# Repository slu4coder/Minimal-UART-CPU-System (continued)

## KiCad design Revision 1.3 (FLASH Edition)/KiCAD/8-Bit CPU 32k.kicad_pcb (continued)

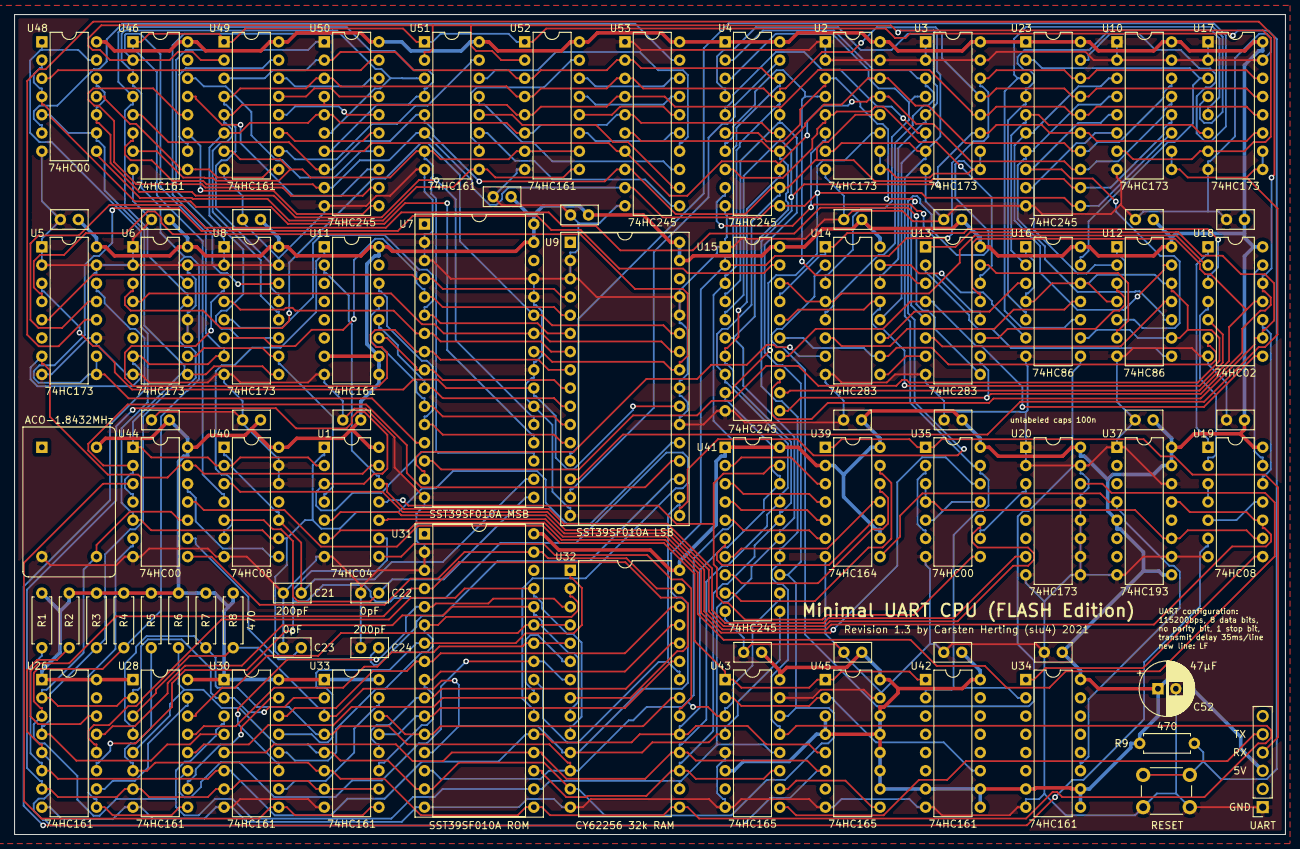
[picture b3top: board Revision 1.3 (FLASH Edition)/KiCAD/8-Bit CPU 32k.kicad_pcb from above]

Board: 2 copper layers, 177.2 x 114.3 mm, 81 parts (0 on the bottom side), 157 nets.

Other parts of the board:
U2, U3: 74HC173; DIP-16_W7.62mm
U4, U15: 74HC245; DIP-20_W7.62mm
U12, U16: 74HC86; DIP-14_W7.62mm
U13, U14: 74HC283; DIP-16_W7.62mm
U18: 74HC02; DIP-14_W7.62mm
U42: 74HC161; DIP-16_W7.62mm
U43, U45: 74HC165; DIP-16_W7.62mm

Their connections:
1.8432MHz: U2.7, U3.7, U42.2; also elsewhere on the board
+5V: U2.16, U3.16, U4.1, U4.20, U12.14, U13.16, U14.16, U15.20, U16.14, U18.14, U42.7, U42.9, U42.10, U42.16, U43.6, U43.16, U45.3, U45.4, U45.10, U45.11, U45.12, U45.13, U45.14, U45.16; also elsewhere on the board
/ALU/A0: U3.3, U4.2, U14.5
/ALU/A1: U3.4, U4.3, U14.3
/ALU/A2: U3.5, U4.4, U14.14
/ALU/A3: U3.6, U4.5, U14.12
/ALU/A4: U2.3, U4.6, U13.5
/ALU/A5: U2.4, U4.7, U13.3
/ALU/A6: U2.5, U4.8, U13.14
/ALU/A7: U2.6, U4.9, U13.12
/ALU/B0: U16.13; also elsewhere on the board
/ALU/B1: U16.10; also elsewhere on the board
/ALU/B2: U16.5; also elsewhere on the board
/ALU/B3: U16.2; also elsewhere on the board
/ALU/B4: U12.13; also elsewhere on the board
/ALU/B5: U12.10; also elsewhere on the board
/ALU/B6: U12.5; also elsewhere on the board
/ALU/B7: U12.2; also elsewhere on the board
/ALU/BUS0: U3.14, U4.18, U15.2, U43.4; also elsewhere on the board
/ALU/BUS1: U3.13, U4.17, U15.3, U43.3; also elsewhere on the board
/ALU/BUS2: U3.12, U4.16, U15.4, U43.14; also elsewhere on the board
/ALU/BUS3: U3.11, U4.15, U15.5, U43.13; also elsewhere on the board
/ALU/BUS4: U2.14, U4.14, U15.6, U43.12; also elsewhere on the board
/ALU/BUS5: U2.13, U4.13, U15.7, U43.11; also elsewhere on the board
/ALU/BUS6: U2.12, U4.12, U15.8, U45.6; also elsewhere on the board
/ALU/BUS7: U2.11, U4.11, U15.9, U45.5; also elsewhere on the board
/ALU/EC: U14.7; also elsewhere on the board
/ALU/ES: U12.1, U12.4, U12.9, U12.12, U16.1, U16.4, U16.9, U16.12; also elsewhere on the board
/ALU/FLAG_C: U13.9; also elsewhere on the board
/ALU/FLAG_N: U13.10, U15.11, U18.12; also elsewhere on the board
/ALU/~EO: U15.19; also elsewhere on the board
/Control Logic/~AI: U2.9, U2.10, U3.9, U3.10; also elsewhere on the board
/Control Logic/~AO: U4.19; also elsewhere on the board
/UART Transmitter/TX: U43.9; also elsewhere on the board
GND: U2.1, U2.2, U2.8, U2.15, U3.1, U3.2, U3.8, U3.15, U4.10, U12.7, U13.8, U14.8, U15.1, U15.10, U16.7, U18.7, U42.8, U43.5, U43.8, U43.15, U45.8, U45.15; also elsewhere on the board
unnamed: U12.3, U13.11
unnamed: U12.6, U13.15
unnamed: U12.8, U13.2
unnamed: U12.11, U13.6
unnamed: U13.1, U15.13, U18.9
unnamed: U13.4, U15.14, U18.8
unnamed: U13.7, U14.9
unnamed: U13.13, U15.12, U18.11
unnamed: U14.1, U15.17, U18.3
unnamed: U14.2, U16.8
unnamed: U14.4, U15.18, U18.2
unnamed: U14.6, U16.11
unnamed: U14.10, U15.15, U18.6
unnamed: U14.11, U16.3
unnamed: U14.13, U15.16, U18.5
unnamed: U14.15, U16.6
unnamed 103: U18.1; also elsewhere on the board
unnamed 104: U18.4; also elsewhere on the board
unnamed 105: U18.10; also elsewhere on the board
unnamed 106: U18.13; also elsewhere on the board
unnamed 129: U42.1, U43.1, U45.1; also elsewhere on the board
unnamed: U42.11, U43.2, U45.2
unnamed: U43.10, U45.9

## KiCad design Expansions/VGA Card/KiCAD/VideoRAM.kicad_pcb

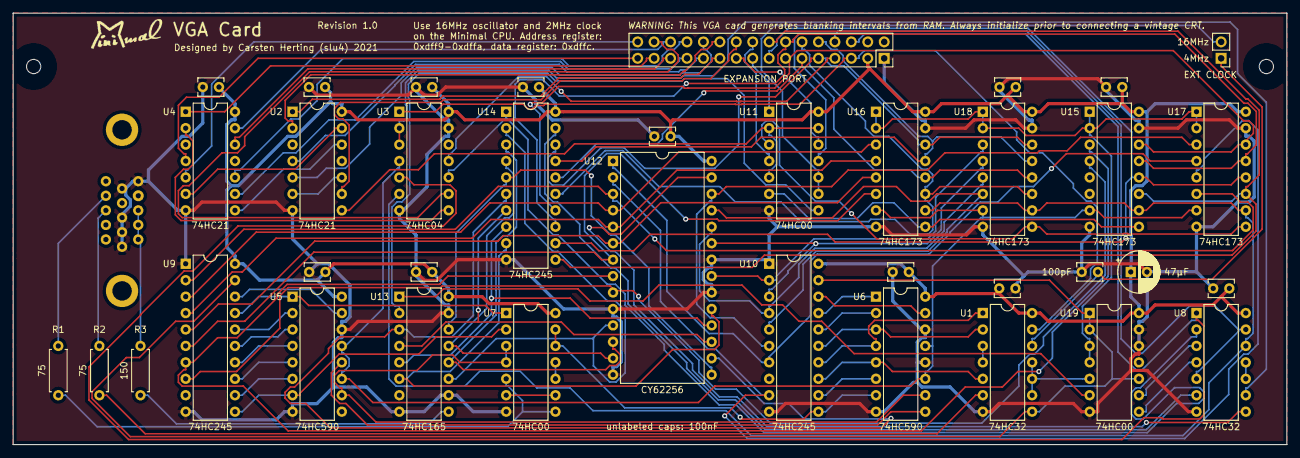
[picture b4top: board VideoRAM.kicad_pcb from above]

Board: 2 copper layers, 196.8 x 66.7 mm, 41 parts (0 on the bottom side), 102 nets.

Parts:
C1: 47µF; CP_Radial_D6.3mm_P2.50mm
C2, C3, C4, C5, C6, C7, C8, C9, C10, C12, C13, C14: 100nF; C_Disc_D3.8mm_W2.6mm_P2.50mm
C11: 100pF; C_Disc_D3.8mm_W2.6mm_P2.50mm
J1: EXPANSION PORT; PinSocket_2x16_P2.54mm_Vertical
J2: VGA connector; VGA DSUB15HD_female
J3: EXT CLOCK; PinHeader_1x02_P2.54mm_Vertical
R1, R2: 75; R_Axial_DIN0207_L6.3mm_D2.5mm_P7.62mm_Horizontal
R3: 150; R_Axial_DIN0207_L6.3mm_D2.5mm_P7.62mm_Horizontal
REF1, REF2: MountingHole_2.2mm_M2
U1, U8: 74HC32; DIP-14_W7.62mm
U2, U4: 74HC21; DIP-14_W7.62mm
U3: 74HC04; DIP-14_W7.62mm
U5, U6: 74HC590; DIP-16_W7.62mm
U7, U11, U19: 74HC00; DIP-14_W7.62mm
U9, U10, U14: 74HC245; DIP-20_W7.62mm
U12: CY62256; DIP-28_W15.24mm
U13: 74HC165; DIP-16_W7.62mm
U15, U16, U17, U18: 74HC173; DIP-16_W7.62mm

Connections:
2MHz: U3.4, U5.11, U5.13, U6.11, U6.13, U15.7, U16.7, U17.7, U18.7
4MHz: C11.1, J3.1, U1.12
16MHz: J3.2, U11.9, U11.10
+5V: C1.1, C2.1, C3.1, C4.1, C5.1, C6.1, C7.1, C8.1, C9.1, C10.1, C12.1, C13.1, C14.1, J1.3, U1.14, U2.14, U3.14, U4.14, U5.16, U6.16, U7.14, U8.14, U9.20, U10.20, U11.14, U12.28, U13.16, U14.20, U15.16, U16.16, U17.16, U18.16, U19.14
/Bus0: J1.9, U14.18, U16.14, U18.14
/Bus1: J1.10, U14.17, U16.13, U18.13
/Bus2: J1.11, U14.16, U16.12, U18.12
/Bus3: J1.12, U14.15, U16.11, U18.11
/Bus4: J1.13, U14.14, U15.14, U17.14
/Bus5: J1.14, U14.13, U15.13, U17.13
/Bus6: J1.15, U14.12, U15.12, U17.12
/Bus7: J1.16, U14.11, U15.11, U17.11
/CLOCK: J1.5, U1.13, U3.1
/H1: U6.15, U10.18
/H2: U6.1, U10.17
/H4: U6.2, U10.16
/H8: U1.2, U6.3, U10.15
/H16: U1.1, U6.4, U10.14
/H32: U1.5, U6.5, U10.13
/M0: J1.17, U11.1
/M1: J1.18, U11.4
/M2: J1.19, U11.12
/M3: J1.20, U2.9
/M4: J1.21, U2.1
/M5: J1.22, U2.2
/M6: J1.23, U2.4
/M7: J1.24, U2.5
/M8: J1.25, U4.9
/M9: J1.26, U4.10
/M10: J1.27, U4.12
/M11: J1.28, U4.13
/M12: J1.29, U4.1
/M13: J1.30, U3.9
/M14: J1.31, U4.4
/M15: J1.32, U4.5
/RI: J1.6, U3.5, U8.1
/RO: U3.10, U8.2, U14.1
/V1: U6.7, U7.12, U7.13, U10.11
/V2: U5.15, U9.18
/V4: U5.1, U7.1, U9.17
/V8: U5.2, U9.16
/V16: U5.3, U9.15
/V32: U5.4, U9.14
/V64: U5.5, U9.13
/V128: U5.6, U9.12
/V256: U5.7, U7.2, U9.11
/VGA_RANGE: U2.8, U11.2, U11.5, U11.13
/~INH: J1.8, U8.5, U8.13, U11.11
/~RI: U3.6, U8.12, U15.10, U16.10, U17.10, U18.10
/~RO: J1.7, U3.11
GND: C1.2, C2.2, C3.2, C4.2, C5.2, C6.2, C7.2, C8.2, C9.2, C10.2, C11.2, C12.2, C13.2, C14.2, J1.1, J2.5, J2.6, J2.7, J2.8, J2.10, U1.7, U2.7, U3.7, U3.13, U4.7, U5.8, U5.14, U6.8, U6.12, U6.14, U7.7, U8.7, U9.1, U9.10, U10.1, U10.10, U11.7, U12.10, U12.14, U12.20, U12.22, U13.8, U13.10, U13.15, U14.10, U15.8, U15.15, U16.8, U16.15, U17.8, U17.15, U18.8, U18.15, U19.7, U19.12, U19.13
unnamed: J2.1, J2.2, J2.3, R3.1
unnamed: J2.13, R2.1
unnamed: J2.14, R1.1
unnamed: R1.2, U7.5, U7.8
unnamed: R2.2, U1.6
unnamed: R3.2, U13.9
unnamed: U1.3, U1.4
unnamed: U1.9, U1.10, U1.11, U19.5
unnamed: U2.6, U2.10
unnamed: U2.12, U4.8
unnamed: U2.13, U4.6
unnamed: U3.8, U4.2
unnamed: U5.10, U6.10, U7.3, U7.4
unnamed: U5.12, U6.9
unnamed: U7.6, U7.9
unnamed: U7.10, U7.11
unnamed: U8.10, U8.11
unnamed: U10.2, U12.21, U18.3
unnamed: U10.3, U12.23, U18.4
unnamed: U10.4, U12.24, U18.5
unnamed: U10.5, U12.25, U18.6
unnamed: U10.6, U12.26, U17.3
unnamed: U10.7, U12.1, U17.4
unnamed: U10.9, U12.2, U17.5
unnamed: U6.6, U10.12
unnamed: U11.3, U17.9, U18.9
unnamed: U11.6, U15.9, U16.9
unnamed: U9.2, U12.3, U17.6
unnamed: U9.3, U12.4, U16.3
unnamed: U9.4, U12.5, U16.4
unnamed: U9.5, U12.6, U16.5
unnamed: U9.6, U12.7, U16.6
unnamed: U9.7, U12.8, U15.3
unnamed: U9.8, U12.9, U15.4
unnamed: U12.11, U13.11, U14.2
unnamed: U12.12, U13.12, U14.3
unnamed: U12.13, U13.13, U14.4
unnamed: U12.15, U13.14, U14.5
unnamed: U12.16, U13.3, U14.6
unnamed: U12.17, U13.4, U14.7
unnamed: U12.18, U13.5, U14.8
unnamed: U12.19, U13.6, U14.9
unnamed: U8.8, U12.27
unnamed: U13.1, U19.6
unnamed: U8.6, U14.19
unnamed: U8.4, U19.8
unnamed: U8.3, U19.9
PIXEL: U11.8, U13.2
T_VRAM: U1.8, U9.19, U10.19, U19.1, U19.2, U19.10
~2MHz: U3.2, U3.3, U8.9
~T_VRAM: U15.1, U15.2, U16.1, U16.2, U17.1, U17.2, U18.1, U18.2, U19.3, U19.4

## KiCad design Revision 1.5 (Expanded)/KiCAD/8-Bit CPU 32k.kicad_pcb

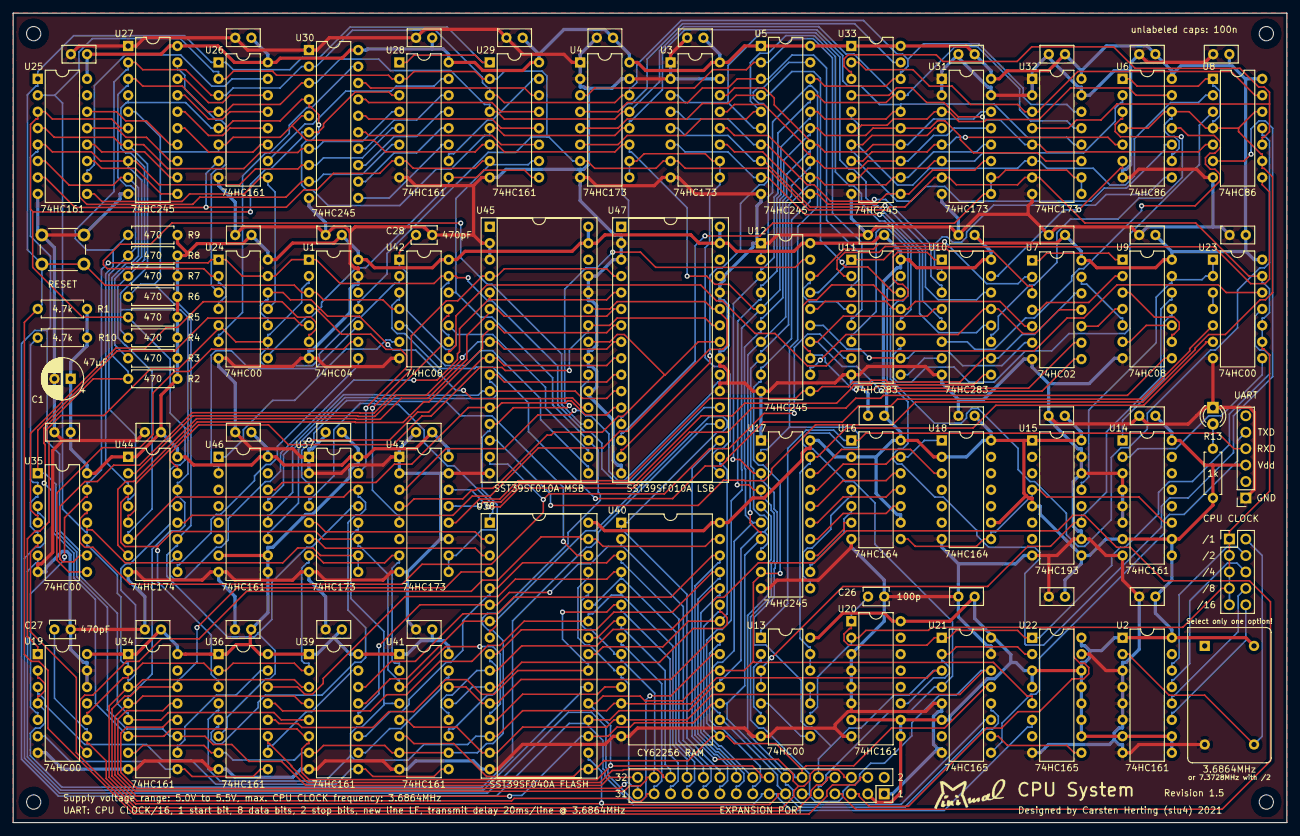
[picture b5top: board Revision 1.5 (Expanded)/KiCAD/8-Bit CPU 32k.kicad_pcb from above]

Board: 2 copper layers, 196.8 x 125.1 mm, 105 parts (0 on the bottom side), 174 nets.

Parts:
C1: 47µF; CP_Radial_D6.3mm_P2.50mm
C2, C3, C4, C5, C6, C7, C8, C9, C10, C11, C12, C13, C14, C15, C16, C17, C18, C19, C20, C21, C22, C23, C24, C25, C29, C30, C31, C32, C33, C34, C35, C36, C37: 100nF; C_Disc_D5.0mm_W2.5mm_P2.50mm
C26: 100p; C_Disc_D3.8mm_W2.6mm_P2.50mm
C27, C28: 470pF; C_Disc_D3.8mm_W2.6mm_P2.50mm
D3: 5V; LED_D3.0mm
H1, H2, H3, H4: M2; MountingHole_2.2mm_M2
J1: UART; PinSocket_1x06_P2.54mm_Vertical
J2: CPU CLOCK; PinHeader_2x05_P2.54mm_Vertical
J3: EXPANSION PORT; PinSocket_2x16_P2.54mm_Vertical
R1, R10: 4.7k; R_Axial_DIN0207_L6.3mm_D2.5mm_P7.62mm_Horizontal
R2, R3, R4, R5, R6, R7, R8, R9: 470; R_Axial_DIN0207_L6.3mm_D2.5mm_P7.62mm_Horizontal
R13: 1k; R_Axial_DIN0207_L6.3mm_D2.5mm_P7.62mm_Horizontal
SW1: RESET; SW_PUSH_6mm
U1: 74HC04; DIP-14_W7.62mm
U2, U14, U20, U25, U26, U28, U29, U34, U36, U39, U41, U46: 74HC161; DIP-16_W7.62mm
U3, U4, U31, U32, U37, U43: 74HC173; DIP-16_W7.62mm
U5, U12, U17, U27, U30, U33: 74HC245; DIP-20_W7.62mm
U6, U8: 74HC86; DIP-14_W7.62mm
U7: 74HC02; DIP-14_W7.62mm
U9, U42: 74HC08; DIP-14_W7.62mm
U10, U11: 74HC283; DIP-16_W7.62mm
U13, U19, U23, U24, U35: 74HC00; DIP-14_W7.62mm
U15: 74HC193; DIP-16_W7.62mm
U16, U18: 74HC164; DIP-14_W7.62mm
U21, U22: 74HC165; DIP-16_W7.62mm
U38: SST39SF040A FLASH; DIP-32_W15.24mm_Socket
U40: CY62256 RAM; DIP-28_W15.24mm
U44: 74HC174; DIP-16_W7.62mm
U45: SST39SF010A MSB; DIP-32_W15.24mm_Socket
U47: SST39SF010A LSB; DIP-32_W15.24mm_Socket
X1: 3.6864MHz; Oscillator_DIP-14

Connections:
+5V: C1.1, C2.1, C3.1, C4.1, C5.1, C6.1, C7.1, C8.1, C9.1, C10.1, C11.1, C12.1, C13.1, C14.1, C15.1, C16.1, C17.1, C18.1, C19.1, C20.1, C21.1, C22.1, C23.1, C24.1, C25.1, C29.1, C30.1, C31.1, C32.1, C33.1, C34.1, C35.1, C36.1, C37.1, J1.3, J3.3, R1.2, R2.1, R3.2, R4.2, R5.2, R6.2, R7.2, R8.2, R9.2, R10.2, R13.2, U1.14, U2.1, U2.7, U2.9, U2.10, U2.16, U3.16, U4.16, U5.1, U5.20, U6.14, U7.14, U8.14, U9.14, U10.16, U11.16, U12.20, U13.14, U14.7, U14.9, U14.10, U14.16, U15.1, U15.5, U15.9, U15.16, U16.2, U16.9, U16.14, U17.20, U18.2, U18.9, U18.14, U19.14, U20.7, U20.9, U20.10, U20.16, U21.6, U21.16, U22.3, U22.4, U22.10, U22.11, U22.12, U22.13, U22.14, U22.16, U23.14, U24.14, U25.16, U26.16, U27.20, U28.16, U29.16, U30.20, U31.16, U32.16, U33.1, U33.20, U34.1, U34.16, U35.14, U36.1, U36.16, U37.16, U38.32, U39.1, U39.16, U40.28, U41.1, U41.16, U42.14, U43.16, U44.1, U44.16, U45.31, U45.32, U46.7, U46.9, U46.10, U46.16, U47.31, U47.32, X1.14
/ALU/A0: U4.3, U5.2, U11.5
/ALU/A1: U4.4, U5.3, U11.3
/ALU/A2: U4.5, U5.4, U11.14
/ALU/A3: U4.6, U5.5, U11.12
/ALU/A4: U3.3, U5.6, U10.5
/ALU/A5: U3.4, U5.7, U10.3
/ALU/A6: U3.5, U5.8, U10.14
/ALU/A7: U3.6, U5.9, U10.12
/ALU/B0: U8.13, U32.3, U33.2
/ALU/B1: U8.10, U32.4, U33.3
/ALU/B2: U8.5, U32.5, U33.4
/ALU/B3: U8.2, U32.6, U33.5
/ALU/B4: U6.13, U31.3, U33.6
/ALU/B5: U6.10, U31.4, U33.7
/ALU/B6: U6.5, U31.5, U33.8
/ALU/B7: U6.2, U31.6, U33.9
/ALU/BUS0: J3.9, R9.1, U4.14, U5.18, U12.2, U17.2, U21.4, U26.3, U27.2, U29.3, U30.2, U32.14, U33.18, U36.3, U37.11, U38.13, U40.11, U41.3, U44.3
/ALU/BUS1: J3.10, R8.1, U4.13, U5.17, U12.3, U17.3, U21.3, U26.4, U27.3, U29.4, U30.3, U32.13, U33.17, U36.4, U37.12, U38.14, U40.12, U41.4, U44.4
/ALU/BUS2: J3.11, R7.1, U4.12, U5.16, U12.4, U17.4, U21.14, U26.5, U27.4, U29.5, U30.4, U32.12, U33.16, U36.5, U37.14, U38.15, U40.13, U41.5, U44.6
/ALU/BUS3: J3.12, R6.1, U4.11, U5.15, U12.5, U17.5, U21.13, U26.6, U27.5, U29.6, U30.5, U32.11, U33.15, U36.6, U37.13, U38.17, U40.15, U41.6, U44.11
/ALU/BUS4: J3.13, R5.1, U3.14, U5.14, U12.6, U17.6, U21.12, U25.3, U27.6, U28.3, U30.6, U31.14, U33.14, U34.3, U38.18, U39.3, U40.16, U44.13
/ALU/BUS5: J3.14, R4.1, U3.13, U5.13, U12.7, U17.7, U21.11, U25.4, U27.7, U28.4, U30.7, U31.13, U33.13, U34.4, U38.19, U39.4, U40.17, U44.14
/ALU/BUS6: J3.15, R3.1, U3.12, U5.12, U12.8, U17.8, U22.6, U25.5, U27.8, U28.5, U30.8, U31.12, U33.12, U34.5, U38.20, U39.5, U40.18
/ALU/BUS7: J3.16, R2.2, U3.11, U5.11, U12.9, U17.9, U22.5, U25.6, U27.9, U28.6, U30.9, U31.11, U33.11, U34.6, U38.21, U39.6, U40.19
/ALU/EC: U11.7, U35.12, U45.15
/ALU/ES: U6.1, U6.4, U6.9, U6.12, U8.1, U8.4, U8.9, U8.12, U45.14
/ALU/FLAG_C: U10.9, U43.13
/ALU/FLAG_N: U7.12, U10.10, U12.11, U43.12
/ALU/FLAG_Z: U9.8, U43.14
/ALU/~EO: U12.19, U43.9, U43.10, U45.13
/Control Logic/CE: U25.7, U26.7, U28.7, U29.7, U29.10, U34.7, U36.7, U39.7, U41.7, U41.10, U42.12, U45.19
/Control Logic/CI: U24.10, U24.12, U45.21
/Control Logic/CO: U24.2, U24.4, U45.20
/Control Logic/Flag0: U43.3, U45.23, U47.23
/Control Logic/Flag1: U43.4, U45.25, U47.25
/Control Logic/Flag2: U43.5, U45.4, U47.4
/Control Logic/HI: U1.1, U19.5, U24.1, U24.13, U35.13, U42.9, U42.13, U47.21
/Control Logic/Inst0: U44.2, U45.8, U47.8
/Control Logic/Inst1: U44.5, U45.7, U47.7
/Control Logic/Inst2: U44.7, U45.6, U47.6
/Control Logic/Inst3: U44.10, U45.5, U47.5
/Control Logic/Inst4: U44.12, U45.27, U47.27
/Control Logic/Inst5: U44.15, U45.26, U47.26
/Control Logic/MI: U19.2, U19.4, U47.20
/Control Logic/RI: C27.2, J3.6, U19.9, U47.19
/Control Logic/Step0: U45.12, U46.14, U47.12
/Control Logic/Step1: U45.11, U46.13, U47.11
/Control Logic/Step2: U45.10, U46.12, U47.10
/Control Logic/Step3: U45.9, U46.11, U47.9
/Control Logic/TI: U23.12, U42.8
/Control Logic/TO: U23.5, U42.3
/Control Logic/~AI: U3.9, U3.10, U4.9, U4.10, U47.17
/Control Logic/~AO: U5.19, U47.15
/Control Logic/~BI: U31.9, U31.10, U32.9, U32.10, U47.14
/Control Logic/~BO: U33.19, U47.13
/Control Logic/~HI: U1.2, U19.1, U24.5, U24.9, U42.2
/Control Logic/~RO: J3.7, U38.24, U40.22, U47.18
/Memory/M0: J3.17, U38.12, U40.21, U41.14
/Memory/M1: J3.18, U38.11, U40.23, U41.13
/Memory/M2: J3.19, U38.10, U40.24, U41.12
/Memory/M3: J3.20, U38.9, U40.25, U41.11
/Memory/M4: J3.21, U38.8, U39.14, U40.26
/Memory/M5: J3.22, U38.7, U39.13, U40.1
/Memory/M6: J3.23, U38.6, U39.12, U40.2
/Memory/M7: J3.24, U38.5, U39.11, U40.3
/Memory/M8: J3.25, U36.14, U38.27, U40.4
/Memory/M9: J3.26, U36.13, U38.26, U40.5
/Memory/M10: J3.27, U36.12, U38.23, U40.6
/Memory/M11: J3.28, U36.11, U38.25, U40.7
/Memory/M12: J3.29, U34.14, U38.4, U40.8
/Memory/M13: J3.30, U34.13, U38.28, U40.9
/Memory/M14: J3.31, U34.12, U38.29, U40.10
/Memory/M15: J3.32, U1.5, U34.11, U35.1
/Memory/~RI_VALID: U19.8, U38.31, U40.27
/UART Receiver/RX: J1.4, U13.1, U16.1
/UART Transmitter/TX: J1.5, U21.9
CLOCK: J2.1, J2.3, J2.5, J2.7, J2.9, J3.5, U1.11, U3.7, U4.7, U13.9, U19.10, U20.2, U23.9, U23.10, U23.13, U25.2, U26.2, U28.2, U29.2, U31.7, U32.7, U34.2, U35.10, U36.2, U37.7, U39.2, U41.2, U43.7
GND: C1.2, C2.2, C3.2, C4.2, C5.2, C6.2, C7.2, C8.2, C9.2, C10.2, C11.2, C12.2, C13.2, C14.2, C15.2, C16.2, C17.2, C18.2, C19.2, C20.2, C21.2, C22.2, C23.2, C24.2, C25.2, C26.1, C27.1, C28.1, C29.2, C30.2, C31.2, C32.2, C33.2, C34.2, C35.2, C36.2, C37.2, D3.1, J1.1, J3.1, SW1.1, U1.7, U1.13, U2.3, U2.4, U2.5, U2.6, U2.8, U3.1, U3.2, U3.8, U3.15, U4.1, U4.2, U4.8, U4.15, U5.10, U6.7, U7.7, U8.7, U9.7, U10.8, U11.8, U12.1, U12.10, U13.7, U14.3, U14.4, U14.5, U14.6, U14.8, U15.8, U15.10, U15.14, U15.15, U16.7, U17.1, U17.10, U18.7, U19.7, U19.12, U19.13, U20.3, U20.4, U20.5, U20.6, U20.8, U21.5, U21.8, U21.15, U22.8, U22.15, U23.7, U24.7, U25.8, U26.8, U27.1, U27.10, U28.8, U29.8, U30.1, U30.10, U31.1, U31.2, U31.8, U31.15, U32.1, U32.2, U32.8, U32.15, U33.10, U34.8, U35.7, U36.8, U37.1, U37.2, U37.8, U38.16, U39.8, U40.14, U41.8, U42.7, U43.1, U43.2, U43.8, U43.11, U43.15, U44.8, U45.2, U45.3, U45.16, U45.22, U45.24, U45.28, U45.29, U46.8, U47.2, U47.3, U47.16, U47.22, U47.24, U47.28, U47.29, X1.7
unnamed: C26.2, U20.1, U21.1, U22.1, U23.11
unnamed: C28.2, U42.1, U42.10, U45.18
unnamed: D3.2, R13.1
unnamed: J2.2, U2.2, X1.8
unnamed: J2.4, U2.14
unnamed: J2.6, U2.13
unnamed: J2.8, U2.12
unnamed: J2.10, U2.11
unnamed: J3.8, R10.1, U35.2, U35.5
unnamed: U1.4, U37.15
unnamed: U1.6, U35.4
unnamed: U1.8, U44.9
unnamed: U1.9, U35.8
unnamed: U1.10, U46.2
unnamed: U7.1, U9.1
unnamed: U7.4, U9.2
unnamed: U7.10, U9.4
unnamed: U7.13, U9.5
unnamed: U9.3, U9.9
unnamed: U9.6, U9.10
unnamed: U7.9, U10.1, U12.13
unnamed: U6.8, U10.2
unnamed: U7.8, U10.4, U12.14
unnamed: U6.11, U10.6
unnamed: U10.7, U11.9
unnamed: U6.3, U10.11
unnamed: U7.11, U10.13, U12.12
unnamed: U6.6, U10.15
unnamed: U7.3, U11.1, U12.17
unnamed: U8.8, U11.2
unnamed: U7.2, U11.4, U12.18
unnamed: U8.11, U11.6
unnamed: U7.6, U11.10, U12.15
unnamed: U8.3, U11.11
unnamed: U7.5, U11.13, U12.16
unnamed: U8.6, U11.15
unnamed: U13.2, U13.6
unnamed: U9.12, U13.3, U13.4, U15.11
unnamed: U13.5, U13.8
unnamed: U13.10, U13.11
unnamed: U13.12, U13.13, U17.19, U23.6
unnamed: U9.11, U14.1
unnamed: U14.2, U23.8
unnamed: U14.11, U15.4, U16.8, U18.8
unnamed: U9.13, U15.13, U23.1, U23.2
unnamed: U16.4, U17.11
unnamed: U16.5, U17.12
unnamed: U16.6, U17.13
unnamed: U16.10, U17.14
unnamed: U16.11, U17.15
unnamed: U16.12, U17.16
unnamed: U16.13, U17.17, U18.1
unnamed: U17.18, U18.3
unnamed: U19.3, U39.9, U41.9
unnamed: U19.6, U34.9, U36.9
unnamed: U20.11, U21.2, U22.2
unnamed: U21.10, U22.9
unnamed: U23.3, U23.4
unnamed: U24.3, U27.19
unnamed: U24.6, U30.19
unnamed: U24.8, U28.9, U29.9
unnamed: U24.11, U25.9, U26.9
unnamed: U25.10, U26.15
unnamed: U25.11, U27.11
unnamed: U25.12, U27.12
unnamed: U25.13, U27.13
unnamed: U25.14, U27.14
unnamed: U26.10, U28.15
unnamed: U26.11, U27.15
unnamed: U26.12, U27.16
unnamed: U26.13, U27.17
unnamed: U26.14, U27.18
unnamed: U28.10, U29.15
unnamed: U28.11, U30.11
unnamed: U28.12, U30.12
unnamed: U28.13, U30.13
unnamed: U28.14, U30.14
unnamed: U29.11, U30.15
unnamed: U29.12, U30.16
unnamed: U29.13, U30.17
unnamed: U29.14, U30.18
unnamed: U34.10, U36.15
unnamed: U35.3, U40.20
unnamed: U35.6, U38.22
unnamed: U35.9, U42.11
unnamed: U35.11, U37.9, U37.10
unnamed: U36.10, U39.15
unnamed: U37.3, U38.30
unnamed: U37.4, U38.1
unnamed: U37.5, U38.2
unnamed: U37.6, U38.3
unnamed: U39.10, U41.15
unnamed: U42.5, U45.17
unnamed: U42.6, U46.1
~RESET: J3.4, R1.1, SW1.2, U1.3, U25.1, U26.1, U28.1, U29.1, U42.4

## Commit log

2021-04-30 Coming soon!
2021-04-30 Source code for YouTube project
2021-04-30 See YouTube video
2021-05-17 Small improvements
2021-06-06 Out now!
2021-08-01 Version 1.5.1
2021-11-24 Emulator release
2021-11-24 Emulator revision 1.5.1
2021-11-24 Emulator revision 1.5.1 released
2021-11-24 Emulator version 1.5.1 released
2021-12-10 GPIO extension card demo
2021-12-17 VGA Extension Card released!
2021-12-17 VGA card released!
2021-12-17 VGA card released
2022-01-25 bug-fix ACB
    Thanks you, paulscottrobson!
2022-01-25 bug-fix in list routine
2022-01-25 version 1.5.2 update
2022-01-25 Revision 1.5.2 update
2022-01-26 Revision 1.5.2
2022-01-26 Revision 1.5.2
    ACB bug-fix - thanks you, paulscottrobson!
2022-01-26 Revision 1.5.2
    ACB bug-fix thanks to paulscottrobson
2022-01-31 bug-fix
    Instruction following '#org <adr>' are now processed correctly.
2022-06-03 Added MIN
2022-06-22 Revision 1.6 Redux
2022-06-23 Added comments about revision 1.6.
2022-07-07 cosmetic updates
2022-07-07 improved random numbers
2022-07-08 4.9MHz upgrade
2022-07-16 Revision 1.6.1
2022-07-19 1.6.2
2023-07-18 Relocating from another repository
2023-07-18 Relocated
2023-07-19 Relocating
2023-08-29 bug-fix in memmove
2023-10-27 Minimal UART Ultra is out!
2023-10-27 Minimal UART Ultra out now!
2023-10-27 Restructuring
